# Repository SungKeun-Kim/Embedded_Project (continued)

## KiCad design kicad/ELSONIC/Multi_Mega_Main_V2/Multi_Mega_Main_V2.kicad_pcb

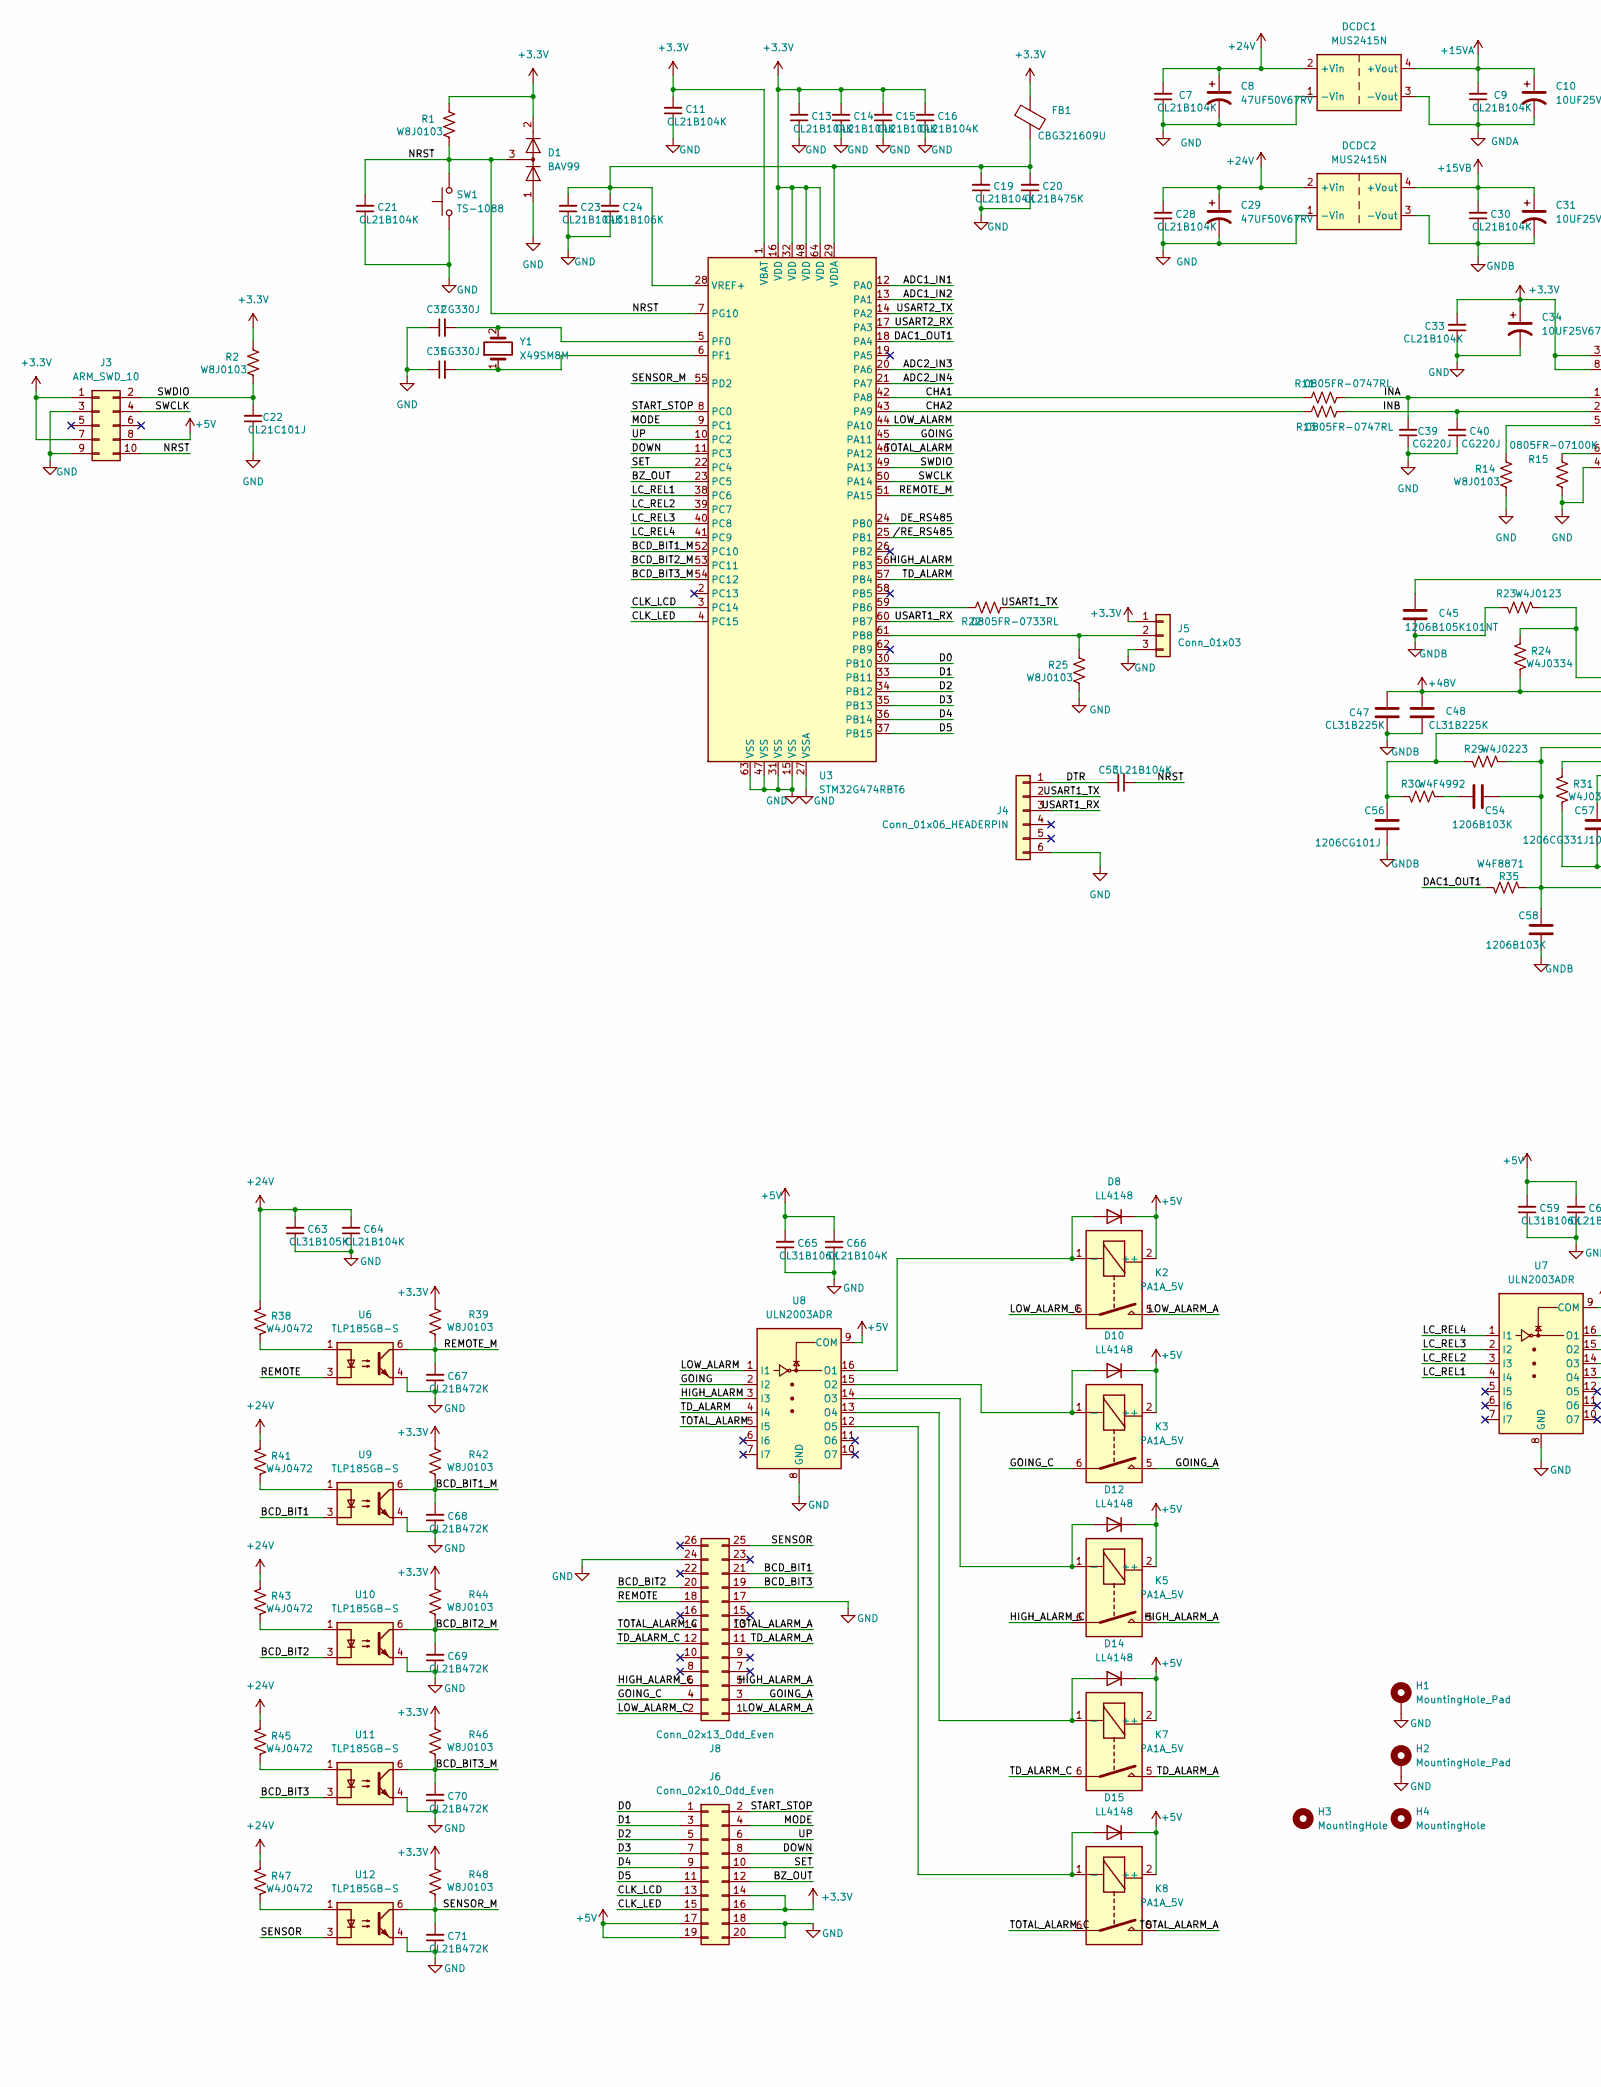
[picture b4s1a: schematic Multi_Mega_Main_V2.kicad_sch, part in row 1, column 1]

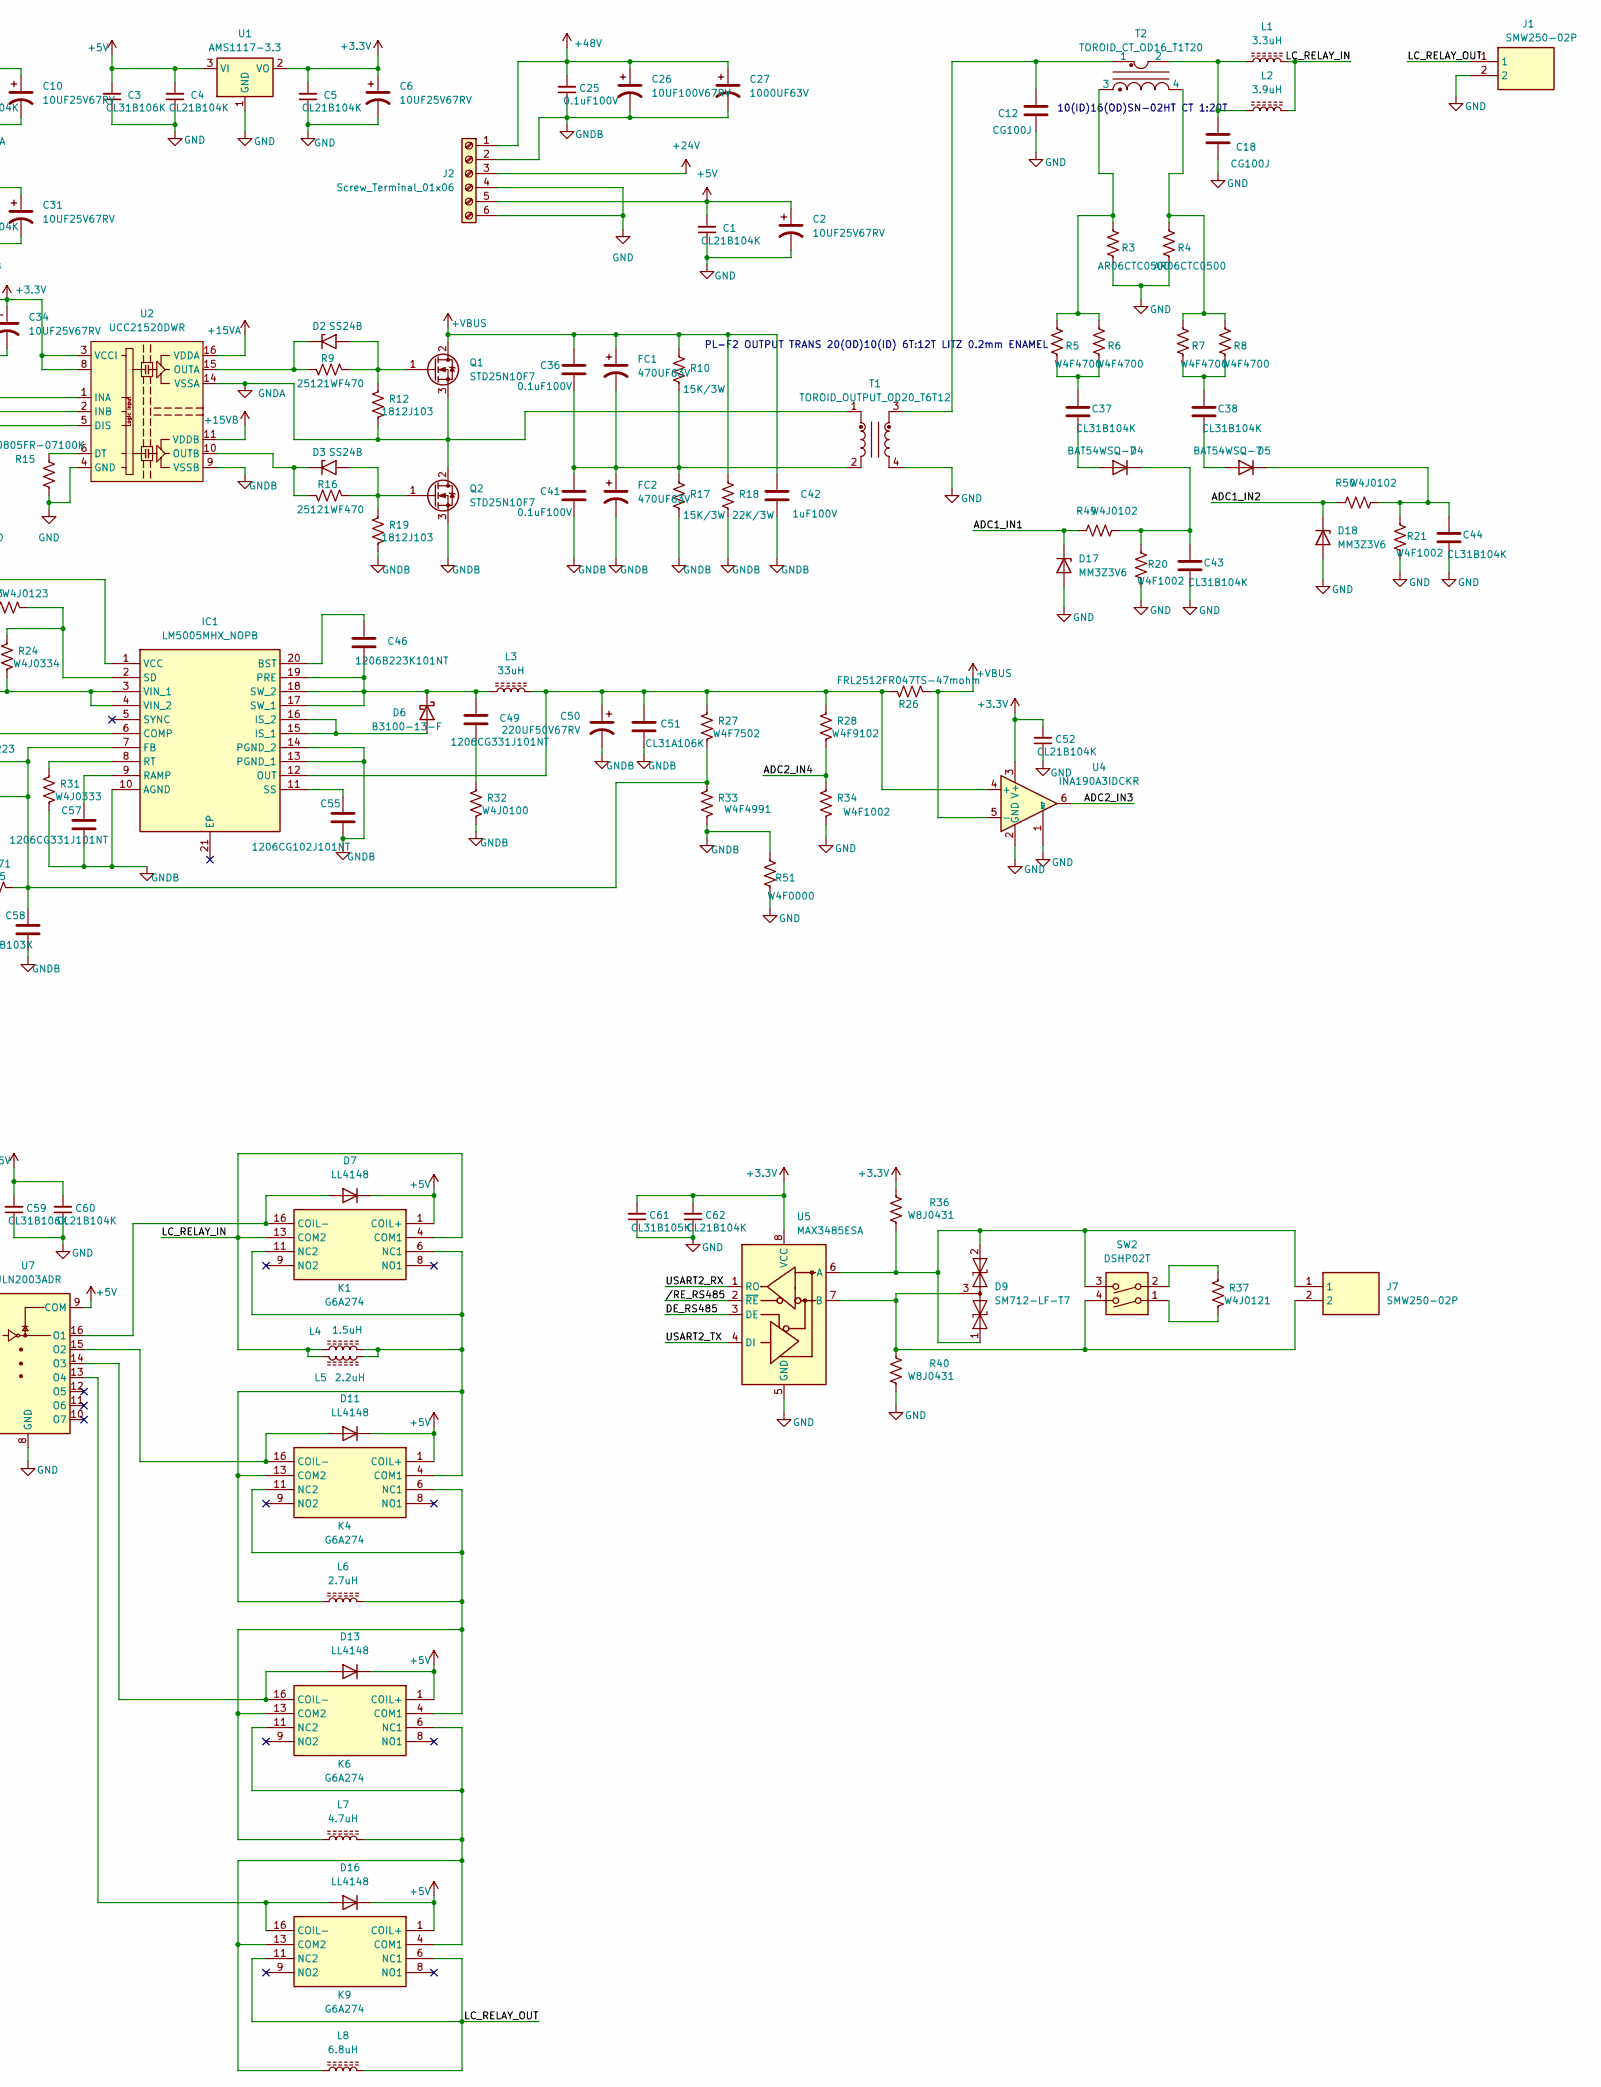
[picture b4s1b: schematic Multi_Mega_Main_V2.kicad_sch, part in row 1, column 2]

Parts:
C1, C4, C5, C7, C9, C11, C13, C14, C15, C16, C19, C21, C23, C28, C30, C33, C52, C53, C60, C62, C64, C66: CL21B104K; C_2012Metric; LCSC C1711
C2, C6, C10, C31, C34: 10UF25V67RV; CP_Elec_4x5.4; LCSC C2895271
C3, C24, C59, C65: CL31B106K; C_3216Metric; LCSC C307369
C8, C29: 47UF50V67RV; CP_Elec_6.3x7.7; LCSC C2887275
C12, C18: CG100J; C_3216Metric; LCSC C1883
C20: CL21B475K; C_2012Metric; LCSC C16194948
C22: CL21C101J; C_2012Metric; LCSC C1790
C25, C36, C41: 0.1uF100V; C_Rect_W7.0mm_P15.00mm
C26: 10UF100V67RV; CP_Elec_6.3x7.7; LCSC C2895274
C27: 1000UF63V; CP_Radial_D16.0mm_P7.50mm
C32, C35: CG330J; C_2012Metric; LCSC C157687
C37, C38, C43, C44: CL31B104K; C_3216Metric; LCSC C1945
C39, C40: CG220J; C_2012Metric; LCSC C24658
C42: 1uF100V; C_Rect_W7.0mm_P15.00mm
C45: 1206B105K101NT; C_3216Metric; LCSC C91151
C46: 1206B223K101NT; C_3216Metric; LCSC C48996
C47, C48: CL31B225K; C_3216Metric; LCSC C39619
C49, C57: 1206CG331J101NT; C_3216Metric; LCSC C20617886
C50: 220UF50V67RV; CP_Elec_10x10.5; LCSC C2887271
C51: CL31A106K; C_3216Metric; LCSC C13585
C54, C58: 1206B103K; C_3216Metric; LCSC C55077
C55: 1206CG102J101NT; C_3216Metric; LCSC C44911
C56: 1206CG101J; C_3216Metric; LCSC C1884
C61, C63: CL31B105K; C_3216Metric; LCSC C13832
C67, C68, C69, C70, C71: CL21B472K; C_2012Metric; LCSC C50131
D1: BAV99; SOT-23; LCSC C68983
D2, D3: SS24B; D_SMB; LCSC C35501
D4, D5: BAT54WSQ-7; D_SOD-323_HandSoldering; LCSC C171824
D6: B3100-13-F; B3100_13_F; LCSC C134447
D7, D8, D10, D11, D12, D13, D14, D15, D16: LL4148; LL4148_MELF; LCSC C84062
D9: SM712-LF-T7; SOT-23; LCSC C2687124
D17, D18: MM3Z3V6; D_SOD-323_HandSoldering; LCSC C12453
DCDC1, DCDC2: MUS2415N
FB1: CBG321609U; R_3216Metric; LCSC C74486
FC1, FC2: 470UF63V; CP_Radial_D12.5mm_P5.00mm
H1, H2: MountingHole_Pad; MTHole_3.5mm_6.8mmPad_GND
H3, H4: MountingHole; MTHole_3.5mm
IC1: LM5005MHX_NOPB; SOP65P640X110-21N; Manufacturer_Part_Number LM5005MHX/NOPB; Mouser Part Number 926-LM5005MHX/NOPB
J1, J7: SMW250-02P; SMW250_02P
J2: Screw_Terminal_01x06; TB_P5.00mm_6P
J3: ARM_SWD_10; IDC-Header_2x05_P2.54mm_Vertical
J4: Conn_01x06_HEADERPIN; PinHeader_1x06_P2.54mm_Vertical
J5: Conn_01x03; PinHeader_1x03_P2.54mm_Vertical
J6: Conn_02x10_Odd_Even; IDC-Header_2x10_P2.54mm_Vertical
J8: Conn_02x13_Odd_Even; IDC-Header_2x13_P2.54mm_Latch_Vertical
K1, K4, K6, K9: G6A274; G6A274PST15USDC12; Manufacturer_Part_Number G6A274PST15USDC12
K2, K3, K5, K7, K8: PA1A_5V; PA1A5V
L1: 3.3uH; L_Radial_D10.0mm_P5.00mm
L2: 3.9uH; L_Radial_D10.0mm_P5.00mm
L3: 33uH; L_Radial_D10.0mm_P5.00mm
L4: 1.5uH; L_Radial_D10.0mm_P5.00mm
L5: 2.2uH; L_Radial_D10.0mm_P5.00mm
L6: 2.7uH; L_Radial_D10.0mm_P5.00mm
L7: 4.7uH; L_Radial_D10.0mm_P5.00mm
L8: 6.8uH; L_Radial_D10.0mm_P5.00mm
Q1, Q2: STD25N10F7; TO-252-2; LCSC C114860
R1, R2, R14, R25, R39, R42, R44, R46, R48: W8J0103; R_2012Metric; LCSC C25612
R3, R4: AR06CTC0500; R_3216Metric; LCSC C5266090
R5, R6, R7, R8: W4F4700; R_3216Metric; LCSC C4502
R9, R16: 25121WF470; R_6332Metric; LCSC C474195
R10, R17: 15K/3W; R_Axial_2W_P20.32mm
R11, R13: 0805FR-0747RL; R_2012Metric; LCSC C114541
R12, R19: 1812J103; R_4532Metric; LCSC C2933913
R15: 0805FR-07100K; R_2012Metric; LCSC C96346
R18: 22K/3W; R_Axial_2W_P20.32mm
R20, R21, R34: W4F1002; R_3216Metric; LCSC C17902
R22: 0805FR-0733RL; R_2012Metric; LCSC C126353
R23: W4J0123; R_3216Metric; LCSC C2771295
R24: W4J0334; R_2012Metric; LCSC C25659
R26: FRL2512FR047TS-47mohm; R_2512_6332Metric; LCSC C7467449
R27: W4F7502; R_3216Metric; LCSC C17986
R28: W4F9102; R_3216Metric; LCSC C17981
R29: W4J0223; R_3216Metric; LCSC C25654
R30: W4F4992; R_3216Metric; LCSC C18017
R31: W4J0333; R_3216Metric; LCSC C25660
R32: W4J0100; R_3216Metric; LCSC C25349
R33: W4F4991; R_3216Metric; LCSC C57609
R35: W4F8871; R_3216Metric; LCSC C55354
R36, R40: W8J0431; R_2012Metric; LCSC C54672
R37: W4J0121; R_3216Metric; LCSC C25351
R38, R41, R43, R45, R47: W4J0472; R_3216Metric; LCSC C26043
R49, R50: W4J0102; R_3216Metric; LCSC C1469
R51: W4F0000; R_3216Metric; LCSC C17888
SW1: TS-1088; SW_SPST_TS-1088-xR025; LCSC C455280
SW2: DSHP02T; CHS-02B_W7.62mm_P1.27mm; LCSC C40735
T1: TOROID_OUTPUT_OD20_T6T12; Toroid_OD20mm_ID10-T6T12
T2: TOROID_CT_OD16_T1T20; Toroid_OD16mm_ID9.6-T1T20
U1: AMS1117-3.3; SOT-223-3_TabPin2; LCSC C6186
U2: UCC21520DWR; SOIC-16W_7.5x10.3mm_P1.27mm; LCSC C601651
U3: STM32G474RBT6; LQFP-64_10x10mm_P0.5mm; LCSC C529413
U4: INA190A3IDCKR; SOT-363_SC-70-6; LCSC C2058578
U5: MAX3485ESA; SOIC-8_3.9x4.9mm_P1.27mm; LCSC C668204
U6, U9, U10, U11, U12: TLP185GB-S; SOIC-4_4.55x3.7mm_P2.54mm; LCSC C388375
U7, U8: ULN2003ADR; SOIC-16_3.9x9.9mm_P1.27mm; LCSC C7512
Y1: X49SM8M; Crystal_SMD_HC49-SD; LCSC C106809

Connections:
+3.3V: C5.2, C6.1, C11.2, C13.2, C14.2, C15.2, C16.2, C33.2, C34.1, C52.2, C61.2, C62.2, D1.2 (A), FB1.1, J3.1, J3.7, J5.1, J6.14, J6.16, R1.2, R2.2, R36.2, R39.2, R42.2, R44.2, R46.2, R48.2, U1.2 (VO), U2.3 (VCCI), U2.8 (VCCI), U3.1 (VBAT), U3.16 (VDD), U3.32 (VDD), U3.48 (VDD), U3.64 (VDD), U4.3 (V+), U5.8 (VCC)
+5V: C1.2, C2.1, C3.2, C4.2, C59.2, C60.2, C65.2, C66.2, D7.1 (K), D8.1 (K), D10.1 (K), D11.1 (K), D12.1 (K), D13.1 (K), D14.1 (K), D15.1 (K), D16.1 (K), J2.5, J3.8, J6.17, J6.19, K1.1 (COIL+), K2.2 (++), K3.2 (++), K4.1 (COIL+), K5.2 (++), K6.1 (COIL+), K7.2 (++), K8.2 (++), K9.1 (COIL+), U1.3 (VI), U7.9 (COM), U8.9 (COM)
+15VA: C9.2, C10.1, DCDC1.4 (+Vout), U2.16 (VDDA)
+15VB: C30.2, C31.1, DCDC2.4 (+Vout), U2.11 (VDDB)
+24V: C7.2, C8.1, C28.2, C29.1, C63.2, C64.2, DCDC1.2 (+Vin), DCDC2.2 (+Vin), J2.3, R38.2, R41.2, R43.2, R45.2, R47.2
+48V: C25.2, C26.1, C27.1, C47.2, C48.2, IC1.3 (VIN_1), IC1.4 (VIN_2), J2.1, R24.1
+VBUS: C36.2, C42.2, FC1.1, Q1.2 (D), R10.2, R18.2, R26.1, U4.5 (-)
/ADC1_IN1: D17.1 (K), R49.2, U3.12 (PA0)
/ADC1_IN2: D18.1 (K), R50.2, U3.13 (PA1)
/ADC2_IN3: U3.20 (PA6), U4.6
/ADC2_IN4: R28.1, R34.2, U3.21 (PA7)
/BCD_BIT1: J8.21, U9.3
/BCD_BIT1_M: C68.2, R42.1, U3.52 (PC10), U9.6
/BCD_BIT2: J8.20, U10.3
/BCD_BIT2_M: C69.2, R44.1, U3.53 (PC11), U10.6
/BCD_BIT3: J8.19, U11.3
/BCD_BIT3_M: C70.2, R46.1, U3.54 (PC12), U11.6
/BZ_OUT: J6.12, U3.23 (PC5)
/CHA1: R11.1, U3.42 (PA8)
/CHA2: R13.1, U3.43 (PA9)
/CLK_LCD: J6.13, U3.3 (PC14)
/CLK_LED: J6.15, U3.4 (PC15)
/D0: J6.1, U3.30 (PB10)
/D1: J6.3, U3.33 (PB11)
/D2: J6.5, U3.34 (PB12)
/D3: J6.7, U3.35 (PB13)
/D4: J6.9, U3.36 (PB14)
/D5: J6.11, U3.37 (PB15)
/DAC1_OUT1: R35.2, U3.18 (PA4)
/DE_RS485: U3.24 (PB0), U5.3 (DE)
/DOWN: J6.8, U3.11 (PC3)
/DTR: C53.2, J4.1
/GOING: U3.45 (PA11), U8.2 (I2)
/GOING_A: J8.3, K3.5
/GOING_C: J8.4, K3.6
/HIGH_ALARM: U3.56 (PB3), U8.3 (I3)
/HIGH_ALARM_A: J8.5, K5.5
/HIGH_ALARM_C: J8.6, K5.6
/INA: C39.2, R11.2, U2.1 (INA)
/INB: C40.2, R13.2, U2.2 (INB)
/LC_REL1: U3.38 (PC6), U7.4 (I4)
/LC_REL2: U3.39 (PC7), U7.3 (I3)
/LC_REL3: U3.40 (PC8), U7.2 (I2)
/LC_REL4: U3.41 (PC9), U7.1 (I1)
/LC_RELAY_IN: K1.4 (COM1), K1.13 (COM2), L1.2, L2.2, L4.1, L5.1
/LC_RELAY_OUT: J1.1, K9.6 (NC1), K9.11 (NC2), L8.2
/LOW_ALARM: U3.44 (PA10), U8.1 (I1)
/LOW_ALARM_A: J8.1, K2.5
/LOW_ALARM_C: J8.2, K2.6
/MODE: J6.4, U3.9 (PC1)
/NRST: C21.2, C53.1, D1.3 (K), J3.10, R1.1, SW1.2, U3.7 (PG10)
/REMOTE: J8.18, U6.3
/REMOTE_M: C67.2, R39.1, U3.51 (PA15), U6.6
/SENSOR: J8.25, U12.3
/SENSOR_M: C71.2, R48.1, U3.55 (PD2), U12.6
/SET: J6.10, U3.22 (PC4)
/START_STOP: J6.2, U3.8 (PC0)
/SWCLK: J3.4, U3.50 (PA14)
/SWDIO: C22.2, J3.2, R2.1, U3.49 (PA13)
/TD_ALARM: U3.57 (PB4), U8.4 (I4)
/TD_ALARM_A: J8.11, K7.5
/TD_ALARM_C: J8.12, K7.6
/TOTAL_ALARM: U3.46 (PA12), U8.5 (I5)
/TOTAL_ALARM_A: J8.13, K8.5
/TOTAL_ALARM_C: J8.14, K8.6
/UP: J6.6, U3.10 (PC2)
/USART1_RX: J4.3, U3.60 (PB7)
/USART1_TX: J4.2, R22.2
/USART2_RX: U3.17 (PA3), U5.1 (RO)
/USART2_TX: U3.14 (PA2), U5.4 (DI)
//RE_RS485: U3.25 (PB1), U5.2 (~RE)
GND: C1.1, C2.2, C3.1, C4.1, C5.1, C6.2, C7.1, C8.2, C11.1, C12.1, C13.1, C14.1, C15.1, C16.1, C18.1, C19.1, C20.1, C21.1, C22.1, C23.1, C24.1, C28.1, C29.2, C32.1, C33.1, C34.2, C35.1, C39.1, C40.1, C43.1, C44.1, C52.1, C59.1, C60.1, C61.1, C62.1, C63.1, C64.1, C65.1, C66.1, C67.1, C68.1, C69.1, C70.1, C71.1, D1.1 (K), D17.2 (A), D18.2 (A), DCDC1.1 (-Vin), DCDC2.1 (-Vin), H1.1 (1_1), H2.1 (1_1), J1.2, J2.4, J2.6, J3.3, J3.9, J4.6, J5.3, J6.18, J6.20, J8.17, J8.24, R3.1, R4.1, R14.1, R15.1, R20.1, R21.1, R25.1, R34.1, R40.1, R51.1, SW1.1, T1.4, U1.1 (GND), U2.4 (GND), U3.15 (VSS), U3.27 (VSSA), U3.31 (VSS), U3.47 (VSS), U3.63 (VSS), U4.1 (REF), U4.2 (GND), U5.5 (GND), U6.4, U7.8 (GND), U8.8 (GND), U9.4, U10.4, U11.4, U12.4
GNDA: C9.1, C10.2, DCDC1.3 (-Vout), Q1.3 (S), Q2.2 (D), R12.1, T1.1, U2.14 (VSSA)
GNDB: C25.1, C26.2, C27.2, C30.1, C31.2, C41.1, C42.1, C45.1, C47.1, C48.1, C50.2, C51.1, C55.1, C56.1, C57.1, C58.1, DCDC2.3 (-Vout), FC2.2, IC1.10 (AGND), IC1.13 (PGND_1), IC1.14 (PGND_2), J2.2, Q2.3 (S), R17.1, R18.1, R19.1, R23.2, R31.1, R32.1, R33.1, R51.2, U2.9 (VSSB)
unnamed: C12.2, T1.3, T2.1
unnamed: C18.2, L1.1, L2.1, T2.2
unnamed: C36.1, C41.2, FC1.2, FC2.1, R10.1, R17.2, T1.2
unnamed: C37.2, R5.1, R6.1
unnamed: C38.2, R7.1, R8.1
unnamed: C49.1, R32.2
unnamed: C54.2, R30.1
unnamed: D2.1 (A1), R9.2, U2.15 (OUTA)
unnamed: D2.2 (A2), Q1.1 (G), R9.1, R12.2
unnamed: D3.1 (A1), R16.2, U2.10 (OUTB)
unnamed: D3.2 (A2), Q2.1 (G), R16.1, R19.2
unnamed: C37.1, D4.2 (A)
unnamed: C43.2, D4.1 (K), R20.2, R49.1
unnamed: C38.1, D5.2 (A)
unnamed: C44.2, D5.1 (K), R21.2, R50.1
unnamed: D6.2 (A), IC1.15 (IS_1), IC1.16 (IS_2)
unnamed: C46.1, C49.2, D6.1 (K), IC1.17 (SW_1), IC1.18 (SW_2), IC1.19 (PRE), L3.1
unnamed: D7.2 (A), K1.16 (COIL-), U7.16 (O1)
unnamed: D8.2 (A), K2.1 (-), U8.16 (O1)
unnamed: D9.1 (A1), D9.2 (A2), J7.1, R36.1, SW2.3, U5.6 (A)
unnamed: D9.3 (common), J7.2, R40.2, SW2.4, U5.7 (B)
unnamed: D10.2 (A), K3.1 (-), U8.15 (O2)
unnamed: D11.2 (A), K4.16 (COIL-), U7.15 (O2)
unnamed: D12.2 (A), K5.1 (-), U8.14 (O3)
unnamed: D13.2 (A), K6.16 (COIL-), U7.14 (O3)
unnamed: D14.2 (A), K7.1 (-), U8.13 (O4)
unnamed: D15.2 (A), K8.1 (-), U8.12 (O5)
unnamed: D16.2 (A), K9.16 (COIL-), U7.13 (O4)
unnamed: C46.2, IC1.20 (BST)
unnamed: C56.2, IC1.6 (COMP), R29.2, R30.2
unnamed: C54.1, C58.2, IC1.7 (FB), R27.1, R29.1, R33.2, R35.1
unnamed: C50.1, C51.2, IC1.12 (OUT), L3.2, R26.2, R27.2, R28.2, U4.4 (+)
unnamed: C57.2, IC1.9 (RAMP)
unnamed: IC1.8 (RT), R31.2
unnamed: IC1.2 (SD), R23.1, R24.2
unnamed: C55.2, IC1.11 (SS)
unnamed: C45.2, IC1.1 (VCC)
unnamed: J5.2, R25.2, U3.61 (PB8)
unnamed: K1.6 (NC1), K1.11 (NC2), K4.4 (COM1), K4.13 (COM2), L4.2, L5.2, L6.1
unnamed: K4.6 (NC1), K4.11 (NC2), K6.4 (COM1), K6.13 (COM2), L6.2, L7.1
unnamed: K6.6 (NC1), K6.11 (NC2), K9.4 (COM1), K9.13 (COM2), L7.2, L8.1
unnamed: R3.2, R5.2, R6.2, T2.3
unnamed: R4.2, R7.2, R8.2, T2.4
unnamed: R37.1, SW2.1
unnamed: R37.2, SW2.2
unnamed: R38.1, U6.1
unnamed: R41.1, U9.1
unnamed: R43.1, U10.1
unnamed: R45.1, U11.1
unnamed: R47.1, U12.1
unnamed: R14.2, U2.5 (DIS)
unnamed: R15.2, U2.6 (DT)
unnamed: R22.1, U3.59 (PB6)
unnamed: C32.2, U3.5 (PF0), Y1.2
unnamed: C35.2, U3.6 (PF1), Y1.1
unnamed: C19.2, C20.2, C23.2, C24.2, FB1.2, U3.28 (VREF+), U3.29 (VDDA)

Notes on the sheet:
PL-F2 OUTPUT TRANS 20(OD)10(ID) 6T:12T LITZ 0.2mm ENAMEL
10(ID)16(OD)SN-02HT CT 1:20T

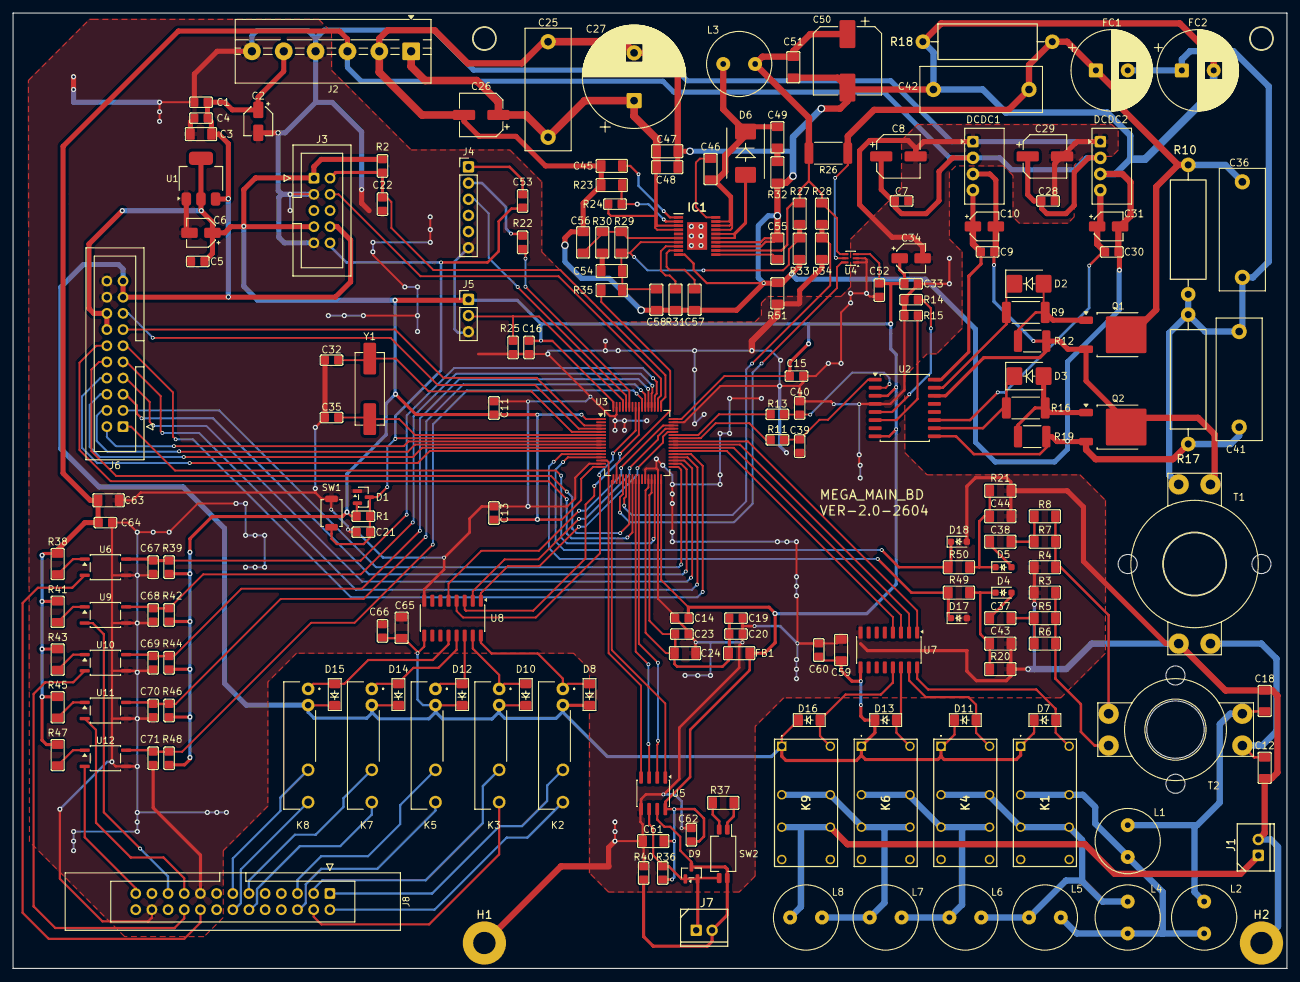
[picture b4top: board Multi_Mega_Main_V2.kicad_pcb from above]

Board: 2 copper layers, 200.0 x 150.0 mm, 193 parts (0 on the bottom side), 130 nets.

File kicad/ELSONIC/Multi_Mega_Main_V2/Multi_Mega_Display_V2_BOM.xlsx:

Comment | Designator | Footprint | LCSC
CL21B104K | C1,C4,C5,C7,C9,C11,C13,C14,C15,C16,C19,C21,C23,C28,C30,C33,C52,C53,C60,C62,C64,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 | C_2012Metric | C1711
10UF25V67RV | C2,C6,C10,C31,C34 | CP_Elec_4x5.4 | C2895271
CL31B106K | C3,C24,C59,C65 | C_3216Metric | C307369
47UF50V67RV | C8,C29 | CP_Elec_6.3x7.7 | C2887275
CG100J | C12,C18 | C_3216Metric | C1883
CL21B475K | C20 | C_2012Metric | C16194948
CL21C101J | C22 | C_2012Metric | C1790
10UF100V67RV | C26 | CP_Elec_6.3x7.7 | C2895274
CG330J | C32,C35 | C_2012Metric | C157687
CL31B104K | C37,C38,C43,C44 | C_3216Metric | C1945
CG220J | C39,C40 | C_2012Metric | C24658
1206B105K101NT | C45 | C_3216Metric | C91151
1206B223K101NT | C46 | C_3216Metric | C48996
CL31B225K | C47,C48 | C_3216Metric | C39619
1206CG331J101NT | C49,C57 | C_3216Metric | C20617886
220UF50V67RV | C50 | CP_Elec_10x10.5 | C2887271
CL31A106K | C51 | C_3216Metric | C13585
1206B103K | C54 | C_3216Metric | C55077
1206CG102J101NT | C55 | C_3216Metric | C44911
1206CG101J | C56 | C_3216Metric | C1884
1206B103K | C58 | C_3216Metric | C55077
CL31B105K | C61,C63 | C_3216Metric | C13832
CL21B472K | C67,C68,C69,C70,C71 | C_2012Metric | C50131
BAV99 | D1 | SOT-23 | C68983
SS24B | D2,D3 | D_SMB | C35501
BAT54WSQ-7 | D4,D5 | D_SOD-323_HandSoldering | C171824
B3100-13-F | D6 | B3100_13_F | C134447
LL4148 | D7,D8,D10,D11,D12,D13,D14,D15,D16 | LL4148_MELF | C84062
SM712-LF-T7 | D9 | SOT-23 | C2687124
MM3Z3V6 | D17,D18 | D_SOD-323_HandSoldering | C12453
CBG321609U | FB1 | R_3216Metric | C74486
LM5005MHX_NOPB | IC1 | SOP65P640X110-21N | C55575
STD25N10F7 | Q1,Q2 | TO-252-2 | C114860
W8J0103 | R1,R2,R14,R25,R39,R42,R44,R46,R48 | R_2012Metric | C25612
AR06CTC0500 | R3,R4 | R_3216Metric | C5266090
W4F4700 | R5,R6,R7,R8 | R_3216Metric | C4502
25121WF470 | R9,R16 | R_6332Metric | C474195
0805FR-0747RL | R11,R13 | R_2012Metric | C114541
1812J103 | R12,R19 | R_4532Metric | C2933913
0805FR-07100K | R15 | R_2012Metric | C96346
W4F1002 | R20,R21,R34 | R_3216Metric | C17902
0805FR-0733RL | R22 | R_2012Metric | C126353
W4J0123 | R23 | R_3216Metric | C2771295
W4J0334 | R24 | R_2012Metric | C25659
FRL2512FR047TS-47mohm | R26 | R_2512_6332Metric | C7467449
W4F7502 | R27 | R_3216Metric | C17986
W4F9102 | R28 | R_3216Metric | C17981
W4J0223 | R29 | R_3216Metric | C25654
W4F4992 | R30 | R_3216Metric | C18017
W4J0333 | R31 | R_3216Metric | C25660
W4J0100 | R32 | R_3216Metric | C25349
W4F4991 | R33 | R_3216Metric | C57609
W4F8871 | R35 | R_3216Metric | C55354
W8J0431 | R36,R40 | R_2012Metric | C54672
W4J0121 | R37 | R_3216Metric | C25351
W4J0472 | R38,R41,R43,R45,R47 | R_3216Metric | C26043
W4J0102 | R49,R50 | R_3216Metric | C1469
W4F0000 | R51 | R_3216Metric | C17888
TS-1088 | SW1 | SW_SPST_TS-1088-xR025 | C455280
DSHP02T | SW2 | CHS-02B_W7.62mm_P1.27mm | C3293412
AMS1117-3.3 | U1 | SOT-223-3_TabPin2 | C6186
UCC21520DWR | U2 | SOIC-16W_7.5x10.3mm_P1.27mm | C601651
STM32G474RBT6 | U3 | LQFP-64_10x10mm_P0.5mm | C529413
INA190A3IDCKR | U4 | SOT-363_SC-70-6 | C2058578
MAX3485ESA | U5 | SOIC-8_3.9x4.9mm_P1.27mm | C668204
TLP185GB-S | U6,U9,U10,U11,U12 | SOIC-4_4.55x3.7mm_P2.54mm | C388375
ULN2003ADR | U7,U8 | SOIC-16_3.9x9.9mm_P1.27mm | C7512
X49SM8M | Y1 | Crystal_SMD_HC49-SD | C106809

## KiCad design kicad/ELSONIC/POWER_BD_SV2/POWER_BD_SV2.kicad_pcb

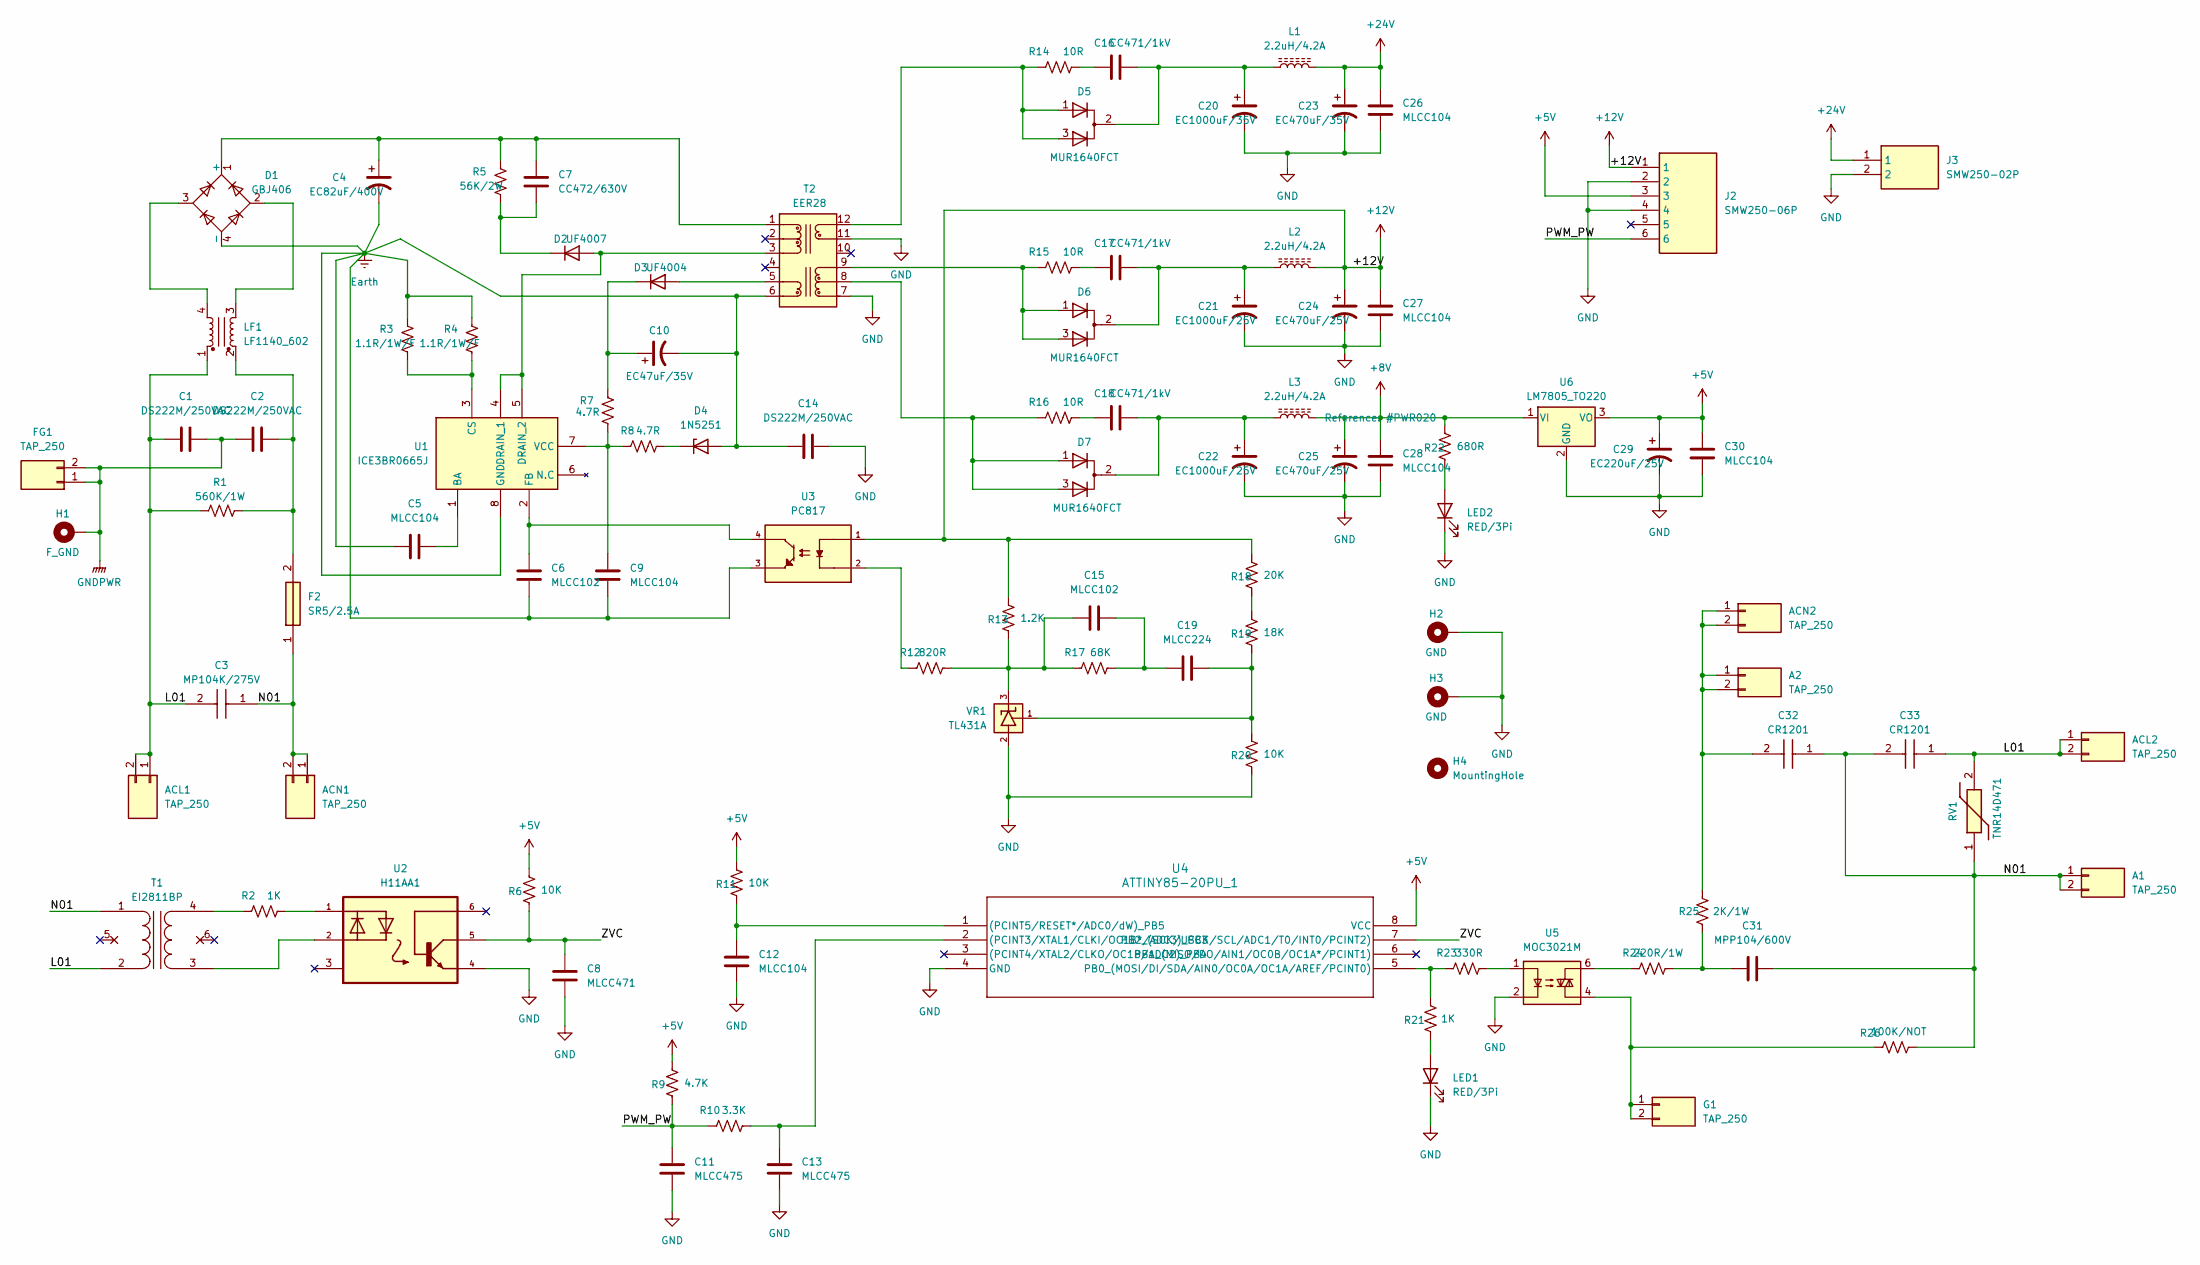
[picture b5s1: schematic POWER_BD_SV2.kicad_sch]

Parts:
A1, A2: TAP_250
ACL1, ACL2: TAP_250
ACN1, ACN2: TAP_250
C1, C2, C14: DS222M/250VAC; DS222M
C3: MP104K/275V; 104K_275V
C4: EC82uF/400V; 82uF_400V
C5, C9, C12, C26, C27, C28, C30: MLCC104; C_3216Metric
C6, C15: MLCC102; C_3216Metric
C7: CC472/630V; C_Disc_D6.0mm_P5.00mm
C8: MLCC471; C_3216Metric
C10: EC47uF/35V; CP_Radial_D5.0mm_P2.00mm
C11, C13: MLCC475; C_3216Metric
C16, C17, C18: CC471/1kV; C_Disc_D4.7mm_P5.00mm
C19: MLCC224; C_3216Metric
C20: EC1000uF/35V; CP_Radial_D12.5mm_P5.00mm
C21, C22: EC1000uF/25V; CP_Radial_D10.0mm_P5.00mm
C23: EC470uF/35V; CP_Radial_D10.0mm_P5.00mm
C24, C25: EC470uF/25V; CP_Radial_D10.0mm_P5.00mm
C29: EC220uF/25V; CP_Radial_D6.3mm_P2.50mm
C31: MPP104/600V; C_PP_L23.0mm_W10.9mm_P21.2mm
C32, C33: CR1201; SPARK_KILLER
D1: GBJ406
D2: UF4007; Diode_P10.16mm
D3: UF4004; Diode_P10.16mm
D4: 1N5251; ZENER_0_5W_P7.62mm_Hori
D5, D6, D7: MUR1640FCT; TO220AB_P2.55mm
F2: SR5/2.5A; SR525ABK
FG1: TAP_250
G1: TAP_250
H1: F_GND; MTHole_3.5mm_7.5mmPad_GND
H2, H3: GND; MTHole_3.5mm_7.5mmPad_GND
H4: MountingHole; MTHole_3.5mm
J2: SMW250-06P; SMW250_06P
J3: SMW250-02P; SMW250_02P
L1, L2, L3: 2.2uH/4.2A; L_Radial_D7.5mm_P3.50mm
LED1, LED2: RED/3Pi; LED_2012Metric
LF1: LF1140_602; LF1140
R1: 560K/1W; R_Axial_1W_P14.6mm
R2, R21: 1K; R_3216Metric
R3, R4: 1.1R/1W/F; R_Axial_1W_P14.6mm
R5: 56K/2W; R_Axial_2W_P20.32mm
R6, R11, R20: 10K; R_3216Metric
R7, R8: 4.7R; R_3216Metric
R9: 4.7K; R_3216Metric
R10: 3.3K; R_3216Metric
R12: 820R; R_3216Metric
R13: 1.2K; R_3216Metric
R14, R15, R16: 10R; R_3216Metric
R17: 68K; R_3216Metric
R18: 20K; R_Axial_0.25W_P10.16mm
R19: 18K; R_Axial_0.25W_P10.16mm
R22: 680R; R_3216Metric
R23: 330R; R_3216Metric
R24: 220R/1W; R_Axial_1W_P14.6mm
R25: 2K/1W; R_Axial_1W_P14.6mm
R26: 100K/NOT; R_Axial_0.25W_P10.16mm
RV1: TNR14D471; TNR14D_P7.62
T1: EI2811BP
T2: EER28; EER28_35_12P
U1: ICE3BR0665J; DIP-8_W7.62mm_Socket
U2: H11AA1; DIP-6_W7.62mm
U3: PC817; DIP-4_W7.62mm_Socket
U4: ATTINY85-20PU_1; DIP-8_W7.62mm_Socket
U5: MOC3021M; DIP-6_W7.62mm
U6: LM7805_TO220; TO220_P2.54mm
VR1: TL431A; TO92_P2.5mm; PARTREV R

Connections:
+5V: C29.1, C30.2, J2.3, R6.2, R9.2, R11.2, U4.8 (VCC), U6.3 (VO)
+8V: C25.1, C28.2, L3.2, R22.2, U6.1 (VI)
+12V: C24.1, C27.2, J2.1, L2.2, R13.2, R18.2, U3.1
+24V: C23.1, C26.2, J3.1, L1.2
/L01: ACL1.1, ACL1.2, ACL2.1, ACL2.2, C1.1, C3.2, C33.1, LF1.1, R1.1, RV1.2, T1.2 (AB)
/N01: A1.1, A1.2, ACN1.1, ACN1.2, C3.1, C31.2, C32.1, C33.2, F2.1, R26.2, RV1.1, T1.1 (AA)
/PWM_PW: C11.2, J2.6, R9.1, R10.1
/ZVC: C8.2, R6.1, U2.5, U4.7 (PB2_(SCK/USCK/SCL/ADC1/T0/INT0/PCINT2))
Earth: C4.2, C5.1, C6.1, C9.1, C10.2, C14.1, D1.4 (-), D4.2 (A), R3.1, R4.1, T2.6 (Vcc_GND), U1.8 (GND), U3.3
GND: C8.1, C11.1, C12.1, C13.1, C14.2, C20.2, C21.2, C22.2, C23.2, C24.2, C25.2, C26.1, C27.1, C28.1, C29.2, C30.1, H2.1, H3.1, J2.2, J2.4, J3.2, LED1.1 (K), LED2.1 (K), R20.1, T2.7 (N_GND1), T2.11 (N_GND2), U2.4, U4.4 (GND), U5.2, U6.2 (GND), VR1.2
GNDPWR: C1.2, C2.1, FG1.1, FG1.2, H1.1
unnamed: A2.1, A2.2, ACN2.1, ACN2.2, C32.2, R25.1
unnamed: C2.2, F2.2, LF1.2, R1.2
unnamed: C15.1, R12.2, R13.1, R17.1, VR1.3
unnamed: C15.2, C19.1, R17.2
unnamed: C16.1, R14.2
unnamed: C17.1, R15.2
unnamed: C18.1, R16.2
unnamed: C19.2, R19.1, R20.2, VR1.1
unnamed: C31.1, R24.2, R25.2
unnamed: C4.1, C7.1, D1.1 (+), R5.1, T2.1 (P0)
unnamed: D1.2, LF1.3
unnamed: D1.3, LF1.4
unnamed: D2.2 (A), T2.3 (P2), U1.4 (DRAIN_1), U1.5 (DRAIN_2)
unnamed: C7.2, D2.1 (K), R5.2
unnamed: D3.2 (A), T2.5 (Vcc)
unnamed: C10.1, D3.1 (K), R7.1
unnamed: D4.1 (K), R8.2
unnamed: C16.2, C20.1, D5.2 (K), L1.1
unnamed: C17.2, C21.1, D6.2 (K), L2.1
unnamed: C18.2, C22.1, D7.2 (K), L3.1
unnamed: G1.1, G1.2, R26.1, U5.4
unnamed: LED1.2 (A), R21.2
unnamed: LED2.2 (A), R22.1
unnamed: R2.2, U2.1
unnamed: R12.1, U3.2
unnamed: R18.1, R19.2
unnamed: R23.2, U5.1
unnamed: R24.1, U5.6
unnamed: T1.3 (SA), U2.2
unnamed: R2.1, T1.4 (SB)
unnamed: D7.1 (A), D7.3 (A), R16.1, T2.8 (N1)
unnamed: D6.1 (A), D6.3 (A), R15.1, T2.9 (N2)
unnamed: D5.1 (A), D5.3 (A), R14.1, T2.12 (N3)
unnamed: C5.2, U1.1 (BA)
unnamed: R3.2, R4.2, U1.3 (CS)
unnamed: C6.2, U1.2 (FB), U3.4
unnamed: C9.2, R7.2, R8.1, U1.7 (VCC)
unnamed: C13.2, R10.2, U4.2 ((PCINT3/XTAL1/CLKI/OC1B*/ADC3)_PB3)
unnamed: C12.2, R11.1, U4.1 ((PCINT5/RESET*/ADC0/dW)_PB5)
unnamed: R21.1, R23.1, U4.5 (PB0_(MOSI/DI/SDA/AIN0/OC0A/OC1A/AREF/PC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)
